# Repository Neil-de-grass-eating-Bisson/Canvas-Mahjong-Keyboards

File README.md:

# Canvas-Mahjong-Keyboards
Both Hi and Low profile 65% left hand numberpad keyboard files.
STEP folder contains both STL and STEP files for easier viewing without CAD software.

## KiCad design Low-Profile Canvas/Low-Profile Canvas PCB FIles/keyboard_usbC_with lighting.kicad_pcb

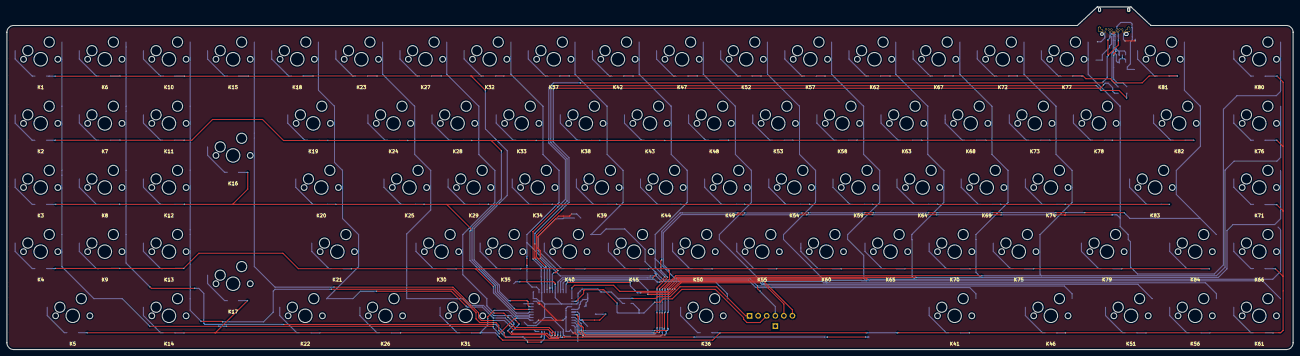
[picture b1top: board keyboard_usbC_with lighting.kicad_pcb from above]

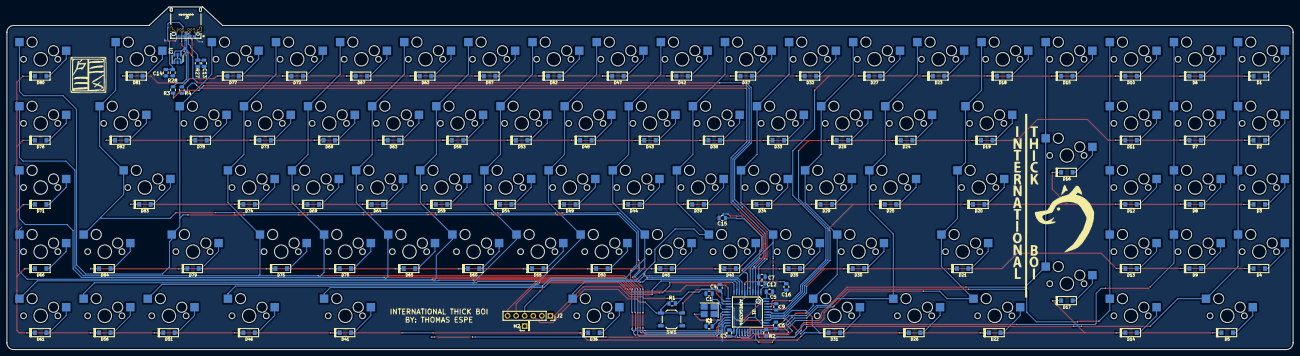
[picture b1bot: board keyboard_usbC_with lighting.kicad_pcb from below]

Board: 2 copper layers, 381.0 x 101.5 mm, 194 parts (110 on the bottom side), 122 nets.

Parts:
C1, C2: 22pF; C_0805_2012Metric
C3, C4, C5, C6, C12, C16: .1u; C_0805_2012Metric
C7: 4.7u; C_0805_2012Metric
C9: .01uF; C_0805_2012Metric
C13, C14: 220pF; C_0805_2012Metric
C15: 1u; C_0805_2012Metric
D1, D2, D3, D4, D5, D6, D7, D8, D9, D10, D11, D12, D13, D14, D15, D16, D17, D18, D19, D20, D21, D22, D23, D24, D25, D26, D27, D28, D29, D30, D31, D32, D33, D34, D35, D36, D37, D38, D39, D40, D41, D42, D43, D44, D45, D46, D47, D48, D49, D50, D51, D52, D53, D54, D55, D56, D57, D58, D59, D60, D61, D62, D63, D64, D65, D66, D67, D68, D69, D70, D71, D72, D73, D74, D75, D76, D77, D78, D79, D80, D81, D82, D83, D84: D; D_SOD123
H2: SHLD; PinHeader_1x01_P2.54mm_Vertical
J2: ICSP; PinSocket_1x06_P2.54mm_Vertical
J3: UJ31-CH-31-SMT-TR; CUI_UJ31-CH-31-SMT-TR
K1, K2, K3, K4, K5, K6, K7, K8, K9, K10, K11, K12, K13, K14, K15, K16, K17, K18, K19, K20, K21, K22, K23, K24, K25, K26, K27, K28, K29, K30, K31, K32, K33, K34, K35, K36, K37, K38, K39, K40, K41, K42, K43, K44, K45, K46, K47, K48, K49, K50, K51, K52, K53, K54, K55, K56, K57, K58, K59, K60, K61, K62, K63, K64, K65, K66, K67, K68, K69, K70, K71, K72, K73, K74, K75, K76, K77, K78, K79, K80, K81, K82, K83, K84: KEYSW; Kailh_socket
R1, R2: 10k; R_0805_2012Metric
R3, R4: 22; R_0805_2012Metric
R27, R28: 5.1K; R_0805_2012Metric
SW1: SW_PUSH; SW_SPST_TL3342
U1: ATMEGA32U4; QFP44
U2: TPD4E1U06; SOT-23-6
X1: XTAL_GND; Crystal_SMD_SeikoEpson_FA238-4Pin_3.2x2.5mm_HandSoldering

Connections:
+5V: C3.2, C4.1, C5.1, C6.1, C7.1, C12.1, C16.2, J2.1, J3.A4, J3.A9, J3.B4, J3.B9, R1.2, U1.2, U1.7, U1.14, U1.24, U1.34, U1.44
CLM0: K1.1, K2.1, K3.1, K4.1, K5.1, U1.36
CLM1: K6.1, K7.1, K8.1, K9.1, U1.32
CLM2: K10.1, K11.1, K12.1, K13.1, K14.1, U1.31
CLM3: K15.1, K16.1, K17.1, U1.28
CLM4: K18.1, K19.1, K20.1, K21.1, K22.1, U1.27
CLM5: K23.1, K24.1, K25.1, K26.1, U1.26
CLM6: K27.1, K28.1, K29.1, K30.1, K31.1, U1.25
CLM7: K32.1, K33.1, K34.1, K35.1, K36.1, U1.1
CLM8: K37.1, K38.1, K39.1, K40.1, K41.1, U1.8
CLM9: J2.4, K42.1, K43.1, K44.1, K45.1, K46.1, U1.9
CLM10: J2.5, K47.1, K48.1, K49.1, K50.1, K51.1, U1.10
CLM11: J2.6, K52.1, K53.1, K54.1, K55.1, K56.1, U1.11
CLM12: K57.1, K58.1, K59.1, K60.1, K61.1, U1.12
CLM13: K62.1, K63.1, K64.1, K65.1, K66.1, U1.18
CLM14: K67.1, K68.1, K69.1, K70.1, K71.1, U1.19
CLM15: K72.1, K73.1, K74.1, K75.1, K76.1, U1.20
CLM16: K77.1, K78.1, K79.1, K80.1, U1.21
CLM17: K81.1, K82.1, K83.1, K84.1, U1.22
unnamed: C9.1, U1.42
unnamed: C13.2, J3.A5, R27.1
unnamed: C14.2, J3.B5, R28.1
unnamed: D1.2, K1.2
unnamed: D2.2, K2.2
unnamed: D3.2, K3.2
unnamed: D4.2, K4.2
unnamed: D5.2, K5.2
unnamed: D6.2, K6.2
unnamed: D7.2, K7.2
unnamed: D8.2, K8.2
unnamed: D9.2, K9.2
unnamed: D10.2, K10.2
unnamed: D11.2, K11.2
unnamed: D12.2, K12.2
unnamed: D13.2, K13.2
unnamed: D14.2, K14.2
unnamed: D15.2, K15.2
unnamed: D16.2, K16.2
unnamed: D17.2, K17.2
unnamed: D18.2, K18.2
unnamed: D19.2, K19.2
unnamed: D20.2, K20.2
unnamed: D21.2, K21.2
unnamed: D22.2, K22.2
unnamed: D23.2, K23.2
unnamed: D24.2, K24.2
unnamed: D25.2, K25.2
unnamed: D26.2, K26.2
unnamed: D27.2, K27.2
unnamed: D28.2, K28.2
unnamed: D29.2, K29.2
unnamed: D30.2, K30.2
unnamed: D31.2, K31.2
unnamed: D32.2, K32.2
unnamed: D33.2, K33.2
unnamed: D34.2, K34.2
unnamed: D35.2, K35.2
unnamed: D36.2, K36.2
unnamed: D37.2, K37.2
unnamed: D38.2, K38.2
unnamed: D39.2, K39.2
unnamed: D40.2, K40.2
unnamed: D41.2, K41.2
unnamed: D42.2, K42.2
unnamed: D43.2, K43.2
unnamed: D44.2, K44.2
unnamed: D45.2, K45.2
unnamed: D46.2, K46.2
unnamed: D47.2, K47.2
unnamed: D48.2, K48.2
unnamed: D49.2, K49.2
unnamed: D50.2, K50.2
unnamed: D51.2, K51.2
unnamed: D52.2, K52.2
unnamed: D53.2, K53.2
unnamed: D54.2, K54.2
unnamed: D55.2, K55.2
unnamed: D56.2, K56.2
unnamed: D57.2, K57.2
unnamed: D58.2, K58.2
unnamed: D59.2, K59.2
unnamed: D60.2, K60.2
unnamed: D61.2, K61.2
unnamed: D62.2, K62.2
unnamed: D63.2, K63.2
unnamed: D64.2, K64.2
unnamed: D65.2, K65.2
unnamed: D66.2, K66.2
unnamed: D67.2, K67.2
unnamed: D68.2, K68.2
unnamed: D69.2, K69.2
unnamed: D70.2, K70.2
unnamed: D71.2, K71.2
unnamed: D72.2, K72.2
unnamed: D73.2, K73.2
unnamed: D74.2, K74.2
unnamed: D75.2, K75.2
unnamed: D76.2, K76.2
unnamed: D77.2, K77.2
unnamed: D78.2, K78.2
unnamed: D79.2, K79.2
unnamed: D80.2, K80.2
unnamed: D81.2, K81.2
unnamed: D82.2, K82.2
unnamed: D83.2, K83.2
unnamed: D84.2, K84.2
unnamed: H2.1, J3.SH1, J3.SH2, J3.SH3, J3.SH4, J3.SH5, J3.SH6
unnamed: R2.2, U1.33
unnamed: R3.1, U1.3
unnamed: R4.1, U1.4
ROW0: D1.1, D6.1, D10.1, D15.1, D18.1, D23.1, D27.1, D32.1, D37.1, D42.1, D47.1, D52.1, D57.1, D62.1, D67.1, D72.1, D77.1, D81.1, U1.41
ROW1: D2.1, D7.1, D11.1, D19.1, D24.1, D28.1, D33.1, D38.1, D43.1, D48.1, D53.1, D58.1, D63.1, D68.1, D73.1, D78.1, D82.1, U1.40
ROW2: D3.1, D8.1, D12.1, D16.1, D20.1, D25.1, D29.1, D34.1, D39.1, D44.1, D49.1, D54.1, D59.1, D64.1, D69.1, D74.1, D83.1, U1.39
ROW3: D4.1, D9.1, D13.1, D21.1, D30.1, D35.1, D40.1, D45.1, D50.1, D55.1, D60.1, D65.1, D70.1, D75.1, D79.1, D84.1, U1.38
ROW4: D5.1, D14.1, D17.1, D22.1, D26.1, D31.1, D36.1, D41.1, D46.1, D51.1, D56.1, D61.1, D66.1, D71.1, D76.1, D80.1, U1.37
UCap: C15.1, U1.6
UGnd: C1.2, C2.2, C3.1, C4.2, C5.2, C6.2, C7.2, C9.2, C12.2, C13.1, C14.1, C15.2, C16.1, J2.2, J3.A1, J3.A12, J3.B1, J3.B12, R2.1, R27.2, R28.2, SW1.1, U1.5, U1.15, U1.23, U1.35, U1.43, U2.2, X1.2, X1.4
USB_+: J3.A6, J3.B6, R4.2, U2.1, U2.3
USB_-: J3.A7, J3.B7, R3.2, U2.4, U2.6
XTAL1: C1.1, U1.16, X1.1
XTAL2: C2.1, U1.17, X1.3
reset: J2.3, R1.1, SW1.2, U1.13
